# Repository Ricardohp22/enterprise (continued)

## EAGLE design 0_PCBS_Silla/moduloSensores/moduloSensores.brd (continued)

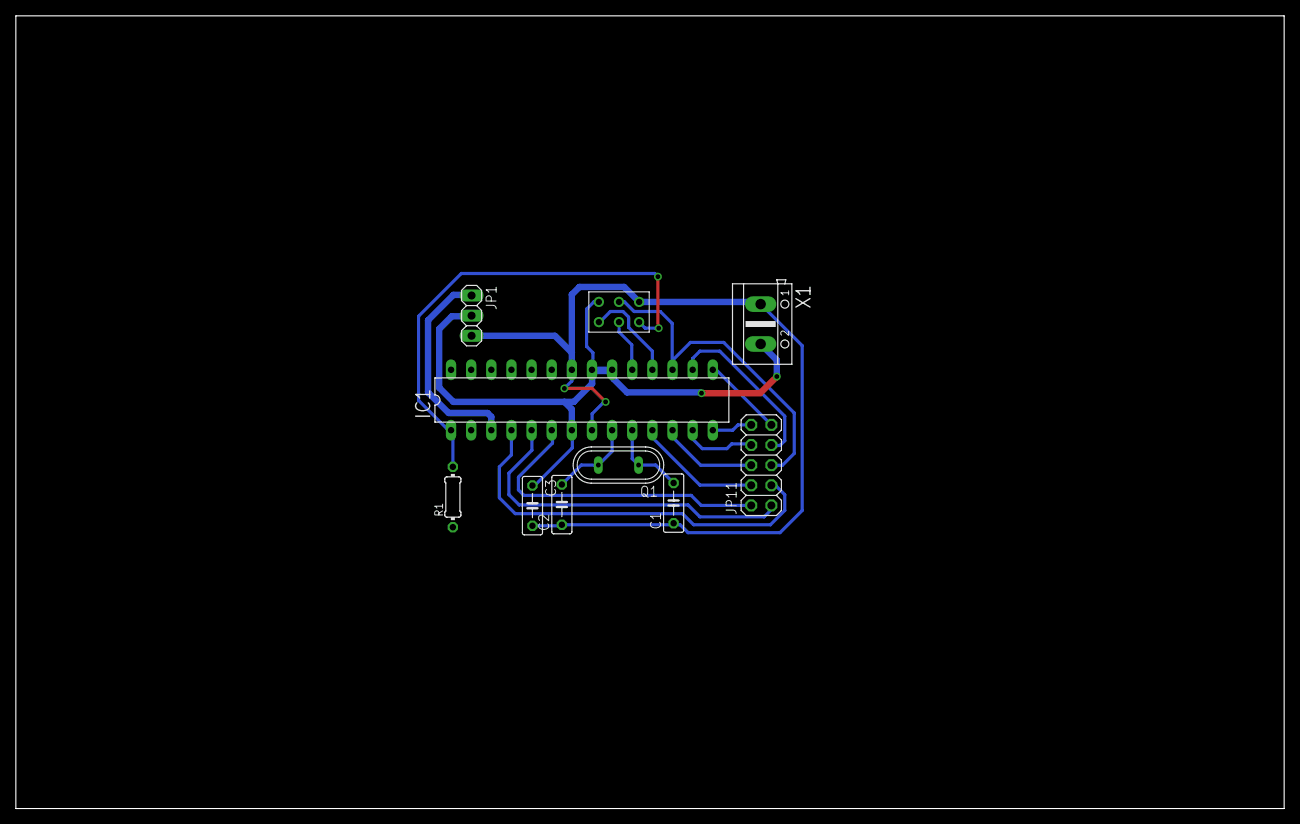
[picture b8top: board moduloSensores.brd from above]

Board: 2 copper layers, 160.0 x 100.0 mm, 10 parts (0 on the bottom side), 19 nets.

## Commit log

2020-03-03 inicio
2020-03-03 solo inserte un comentario al innicio del codigo
2020-03-03 iniciando repo completo
2020-03-03 Bump bower from 1.2.8 to 1.8.8 in /grafica_xyz/morris.js-0.5.1
    Bumps [bower](https://github.com/bower/bower) from 1.2.8 to 1.8.8.
    - [Release notes](https://github.com/bower/bower/releases)
    - [Changelog](https://github.com/bower/bower/blob/master/CHANGELOG.md)
    - [Commits](https://github.com/bower/bower/compare/v1.2.8...v1.8.8)
2020-03-03 borra gitignore
2020-03-03 borra grafica_xyz
2020-03-03 haciendo prueba de modificaciones desde empresa
2020-03-04 4 marzo
2020-03-06 6 marzo 2020
2020-03-09 9 marzo 2020
2020-03-10 modificaciones a codigo de transmisor
2020-03-11 correccion de ofset en gorra
2020-03-11 11 marzo 2020
2020-03-12 12 marzo 2020
2020-03-13 13 marzo 2020
2020-03-13 rel componentes
2020-03-17 17 marzo 2020
2020-03-20 20 marzo 2020
2020-09-02 Bump bl from 3.0.0 to 3.0.1 in /SerialCom-web
    Bumps [bl](https://github.com/rvagg/bl) from 3.0.0 to 3.0.1.
    - [Release notes](https://github.com/rvagg/bl/releases)
    - [Commits](https://github.com/rvagg/bl/compare/v3.0.0...v3.0.1)
2020-12-12 Bump ini from 1.3.5 to 1.3.8 in /SerialCom-web
    Bumps [ini](https://github.com/isaacs/ini) from 1.3.5 to 1.3.8.
    - [Release notes](https://github.com/isaacs/ini/releases)
    - [Commits](https://github.com/isaacs/ini/compare/v1.3.5...v1.3.8)
2021-01-21 Bump socket.io from 2.3.0 to 2.4.0 in /SerialCom-web
    Bumps [socket.io](https://github.com/socketio/socket.io) from 2.3.0 to 2.4.0.
    - [Release notes](https://github.com/socketio/socket.io/releases)
    - [Changelog](https://github.com/socketio/socket.io/blob/2.4.0/CHANGELOG.md)
    - [Commits](https://github.com/socketio/socket.io/compare/2.3.0...2.4.0)
2021-06-30 Bump socket.io-parser from 3.3.0 to 3.3.2 in /SerialCom-web
    Bumps [socket.io-parser](https://github.com/socketio/socket.io-parser) from 3.3.0 to 3.3.2.
    - [Release notes](https://github.com/socketio/socket.io-parser/releases)
    - [Changelog](https://github.com/socketio/socket.io-parser/blob/3.3.2/CHANGELOG.md)
    - [Commits](https://github.com/socketio/socket.io-parser/compare/3.3.0...3.3.2)
    ---
    updated-dependencies:
2022-11-09 Bump socket.io-parser from 3.3.0 to 3.3.3 in /SerialCom-web
    Bumps [socket.io-parser](https://github.com/socketio/socket.io-parser) from 3.3.0 to 3.3.3.
    - [Release notes](https://github.com/socketio/socket.io-parser/releases)
    - [Changelog](https://github.com/socketio/socket.io-parser/blob/main/CHANGELOG.md)
    - [Commits](https://github.com/socketio/socket.io-parser/compare/3.3.0...3.3.3)
    ---
    updated-dependencies:
2022-11-23 Bump engine.io and socket.io in /SerialCom-web
    Bumps [engine.io](https://github.com/socketio/engine.io) to 3.6.1 and updates ancestor dependency [socket.io](https://github.com/socketio/socket.io). These dependencies need to be updated together.
    Updates `engine.io` from 3.4.0 to 3.6.1
    - [Release notes](https://github.com/socketio/engine.io/releases)
    - [Changelog](https://github.com/socketio/engine.io/blob/main/CHANGELOG.md)
    - [Commits](https://github.com/socketio/engine.io/compare/3.4.0...3.6.1)
    Updates `socket.io` from 2.3.0 to 2.5.0
2022-12-07 Bump qs and express in /SerialCom-web
    Bumps [qs](https://github.com/ljharb/qs) to 6.11.0 and updates ancestor dependency [express](https://github.com/expressjs/express). These dependencies need to be updated together.
    Updates `qs` from 6.7.0 to 6.11.0
    - [Release notes](https://github.com/ljharb/qs/releases)
    - [Changelog](https://github.com/ljharb/qs/blob/main/CHANGELOG.md)
    - [Commits](https://github.com/ljharb/qs/compare/v6.7.0...v6.11.0)
    Updates `express` from 4.17.1 to 4.18.2
2022-12-12 Bump express from 4.17.1 to 4.17.3 in /SerialCom-web
    Bumps [express](https://github.com/expressjs/express) from 4.17.1 to 4.17.3.
    - [Release notes](https://github.com/expressjs/express/releases)
    - [Changelog](https://github.com/expressjs/express/blob/master/History.md)
    - [Commits](https://github.com/expressjs/express/compare/4.17.1...4.17.3)
    ---
    updated-dependencies:
